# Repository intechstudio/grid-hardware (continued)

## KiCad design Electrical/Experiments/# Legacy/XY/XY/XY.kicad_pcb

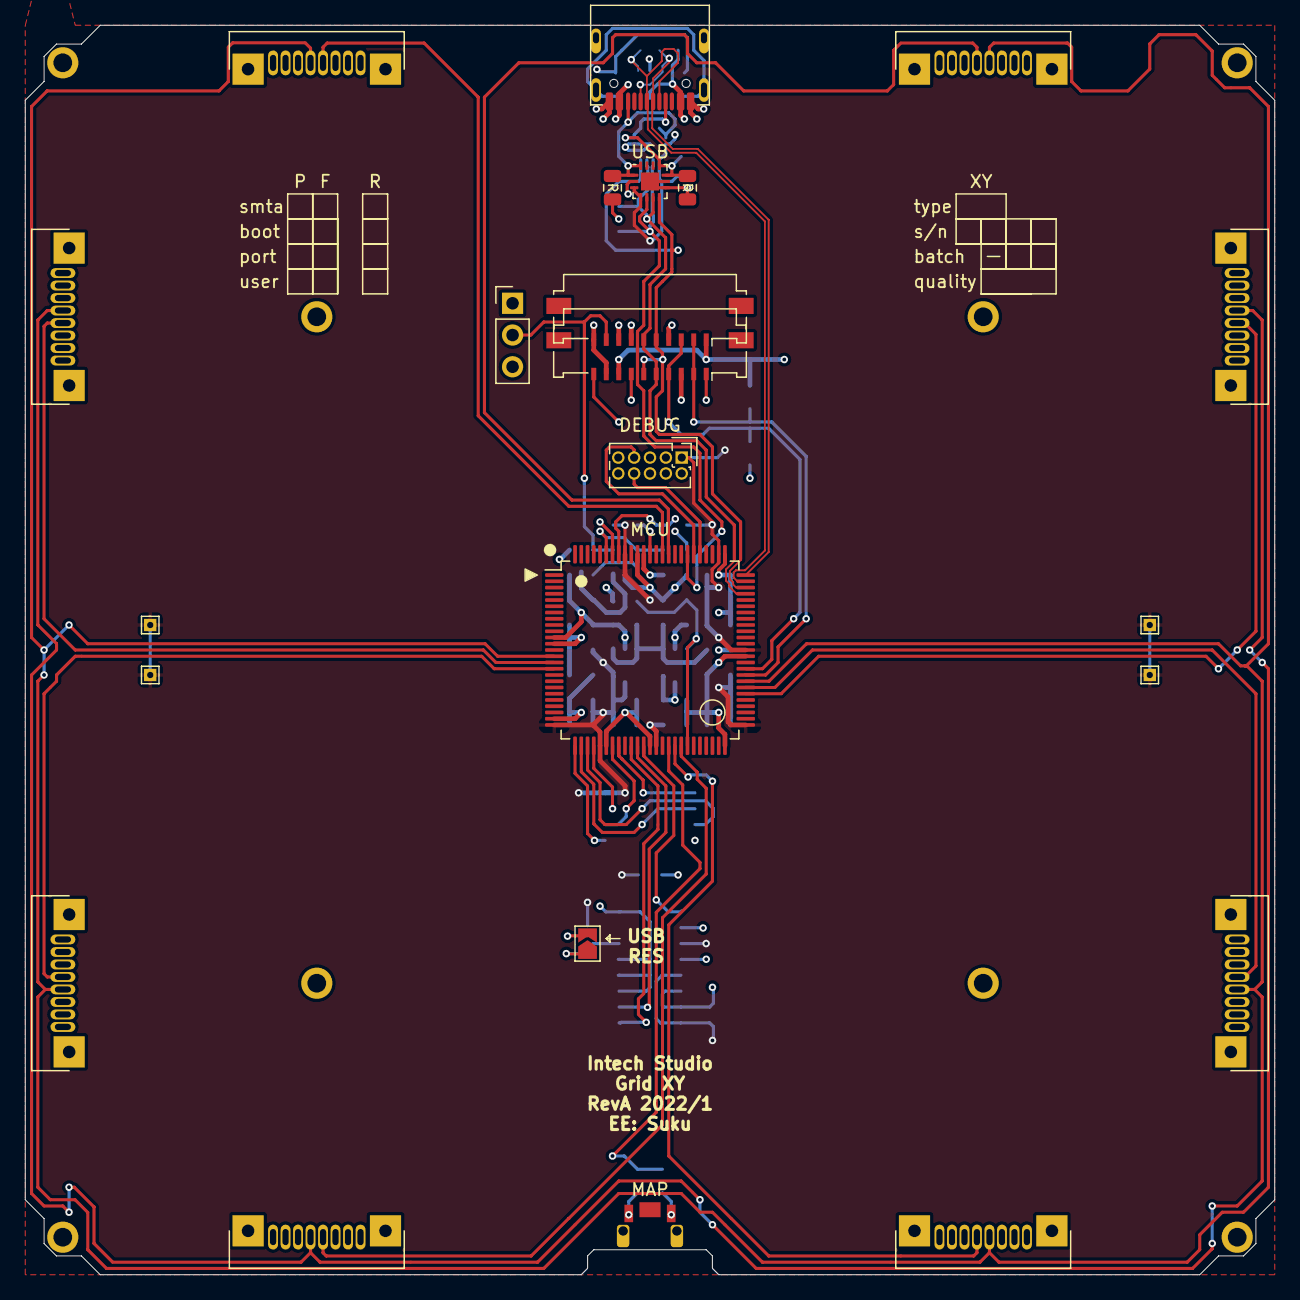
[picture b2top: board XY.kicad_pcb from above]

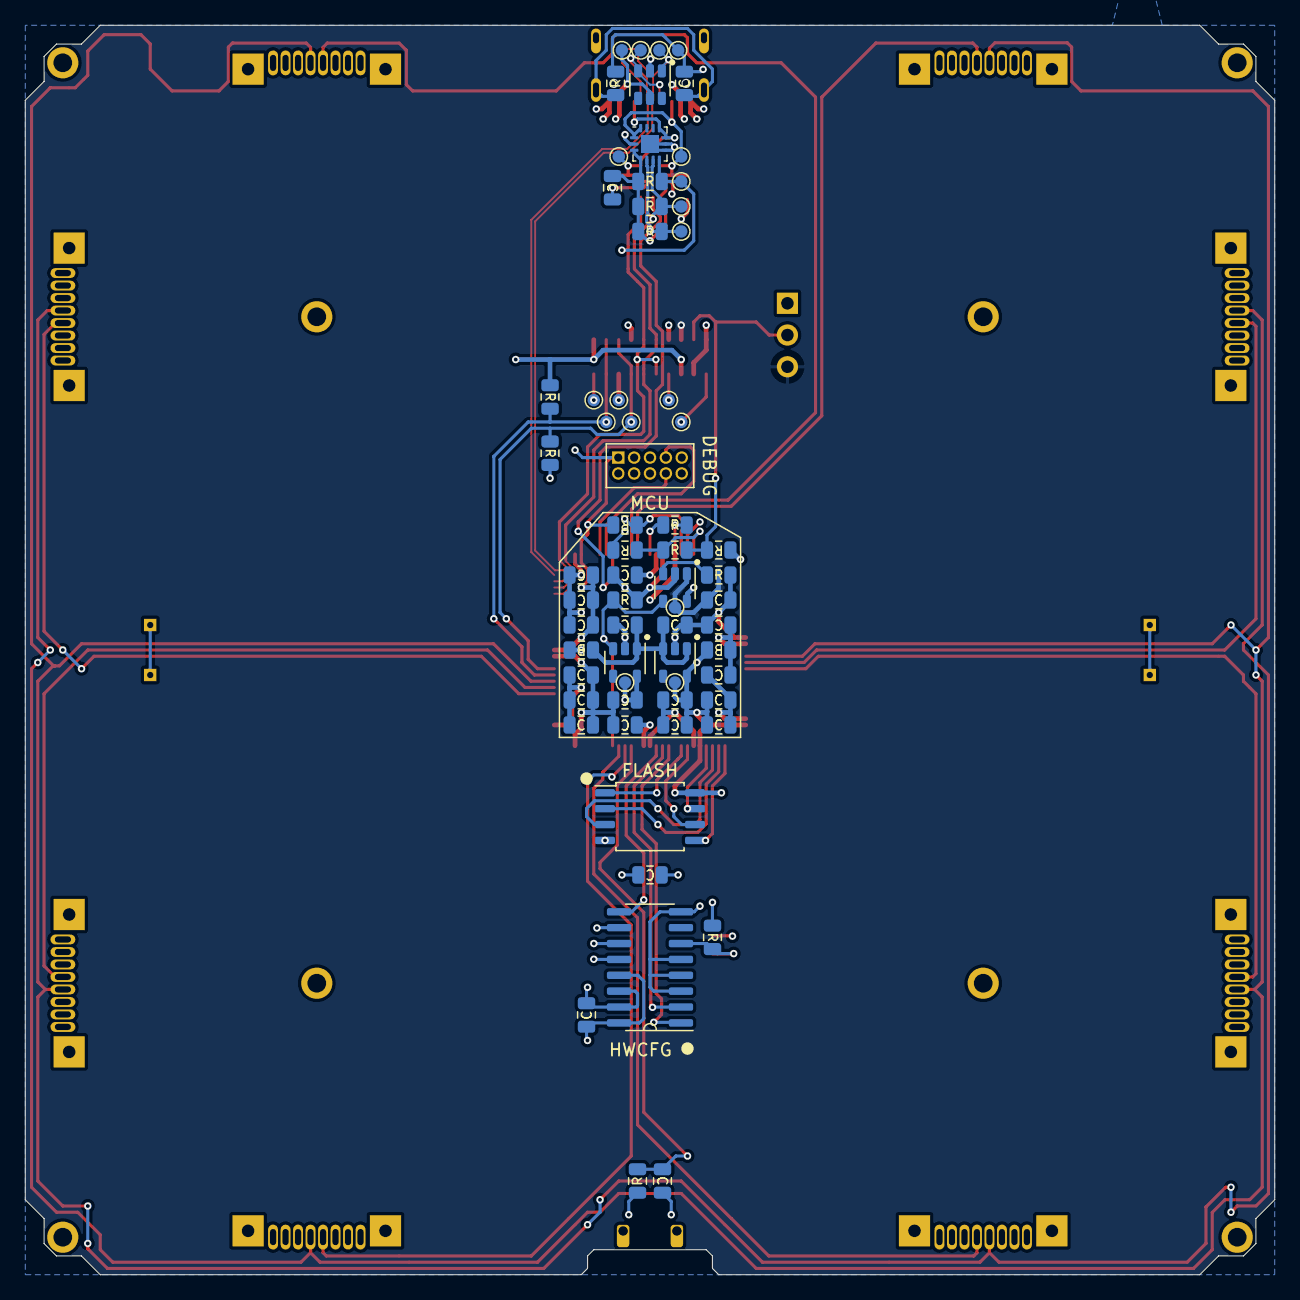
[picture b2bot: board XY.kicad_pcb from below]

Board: 4 copper layers, 100.0 x 100.0 mm, 89 parts (65 on the bottom side), 53 nets.

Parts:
C33, C39, C41, C42, C44, C45, C46, C47, C48, C49, C51, C54, C55, C94, C95: 100n; CAP_0805
C34, C36, C40, C50, C53: 1u; CAP_0805
C37: 4n7; CAP_0805
C38, C43: 10u; CAP_0805
J1: USB_C_TYPE-C-32-M-12; USB_C_Korean_Hroparts_TYPE-C-31-M-12
J2: (NF); PinHeader_2x05_P1.27mm_Vertical
J3: (NF); PinHeader_1x03_P2.54mm_Vertical
J4, J5, J6, J7, J8, J9, J10, J11: C20110 (NF); grid_ffc_8_vertical
J12: C262716; Molex_200528-0100_1x10-1MP_P1.00mm_Horizontal
J13: C262716 (NF); Molex_200528-0100_1x10-1MP_P1.00mm_Horizontal
JP2: (NF); SolderJumper-2_P1.3mm_Open_TrianglePad1.0x1.5mm
L1, L2: GZ2012D601TF; FERRIT_0805
M1: (NF); grid_outline
R1, R2, R36, R111, R112: 10k; RES_0805
R34, R37, R107, R108, R109, R110: 5k1; RES_0805
R35: 1M; RES_0805
R38, R39, R40, R41, R42: 1k; RES_0805
SW1: C255807; SW_HYP_MAPMODE
TP1, TP2, TP3, TP4: TestPoint; TestPoint_THTPad_1.0x1.0mm_Drill0.5mm
TP5: D-; TestPoint_Pad_D1.0mm
TP6: D+; TestPoint_Pad_D1.0mm
TP7: GND; TestPoint_Pad_D1.0mm
TP8: VB; TestPoint_Pad_D1.0mm
TP9: UC; TestPoint_Pad_D1.0mm
TP10: UI; TestPoint_Pad_D1.0mm
TP11: UI_5V; TestPoint_Pad_D1.0mm
TP12: MXT_DSS; TestPoint_Pad_D1.0mm
TP13: MXT_DDATA; TestPoint_Pad_D1.0mm
TP14: MXT_DCLK; TestPoint_Pad_D1.0mm
TP15: MXT_INT; TestPoint_Pad_D1.0mm
TP16: SDA; TestPoint_Pad_D1.0mm
TP17: SCL; TestPoint_Pad_D1.0mm
TP18: INT; TestPoint_Pad_D1.0mm
TP19: CC1; TestPoint_Pad_D1.0mm
TP20: CC2; TestPoint_Pad_D1.0mm
TP21: MXT_RST; TestPoint_Pad_D1.0mm
TP22: MXT_GND; TestPoint_Pad_D1.0mm
U3: 74HC165; SOIC-16_74HC165
U4: SESRV05-4; SOT-23-6
U5, U6: LN1134A332MR-G; SOT-23-5
U7: SAMD51N20A; TQFP-100_14x14mm_P0.5mm
U8: W25Q16JVSSIQ; SOIC-8W_FLASH
U15, U16: FUSB302BMPX (NF); WQFN-14-1EP_2.5x2.5mm_P0.5mm_EP1.45x1.45mm
U17: MT9700; SOT-23-5

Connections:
+3V3_UC: C33.1, C40.1, C41.1, C42.1, C43.1, C44.1, C45.1, C46.1, C47.1, C48.1, C51.1, C54.1, C55.1, C94.1, J2.1, L1.2, R38.2, R39.2, R108.1, R109.1, R110.1, R112.1, TP1.1, TP2.1, TP3.1, TP4.1, TP9.1, U3.11, U3.13, U3.16, U5.5, U7.25, U7.30, U7.39, U7.51, U7.63, U7.77, U7.92, U8.8, U15.3, U15.4, U16.3, U16.4
+3V3_UI: C36.1, J12.8, J13.1, R1.1, TP10.1, U6.5
+5V: J1.A4B9, J1.A9B4, J4.1, J4.2, J4.3, J5.6, J5.7, J5.8, J6.6, J6.7, J6.8, J7.1, J7.2, J7.3, J8.1, J8.2, J8.3, J9.6, J9.7, J9.8, J10.6, J10.7, J10.8, J11.1, J11.2, J11.3, L2.2, R34.1, TP8.1, U4.5, U15.2, U16.2, U17.5
+5V_UI: C50.1, J3.3, J13.8, TP11.1, U17.1
/HWCFG/HWCFG_CLOCK: U3.2, U7.36
/HWCFG/HWCFG_DATA: U3.9, U7.37
/HWCFG/HWCFG_SHIFT: U3.1, U7.35
/MCU/GRID_AUX_RX: J2.8, U7.80
/MCU/GRID_AUX_TX: J2.7, U7.81
/MCU/GRID_EAST_RX: J7.4, U7.56
/MCU/GRID_EAST_TX: J9.5, U7.57
/MCU/GRID_NORTH_RX: J4.4, U7.86
/MCU/GRID_NORTH_TX: J5.5, U7.85
/MCU/GRID_SOUTH_RX: J11.4, U7.42
/MCU/GRID_SOUTH_TX: J10.5, U7.43
/MCU/GRID_SYNC_1: J5.4, J6.4, J9.4, J10.4, U7.58
/MCU/GRID_SYNC_2: J4.5, J7.5, J8.5, J11.5, U7.14
/MCU/GRID_WEST_RX: J8.4, U7.16
/MCU/GRID_WEST_TX: J6.5, U7.15
/MCU/MAP_MODE: C95.1, R40.2, U7.41
/MCU/MUX_ADDRESS_A: J12.2, J13.2, R1.2, TP15.1, U7.59
/MCU/MUX_ADDRESS_B: J12.4, J13.3, R2.1, TP21.1, U7.60
/MCU/QSPI_IO_0: U7.26, U8.5
/MCU/QSPI_IO_1: U7.27, U8.2
/MCU/QSPI_IO_2: U7.28, U8.3
/MCU/QSPI_IO_3: U7.29, U8.7
/MCU/QSPI_SCK: U7.32, U8.6
/MCU/QSPI_~CE: U7.33, U8.1
/MCU/SYS_I2C_INT_0: R110.2, TP18.1, U7.82, U15.5, U16.5
/MCU/SYS_RESET: J2.10, R38.1, U7.88
/MCU/SYS_SWCLK: J2.4, R39.1, U7.93
/MCU/SYS_SWDIO: J2.2, U7.94
/MCU/SYS_SWO: J2.6, R41.2
/MCU/Sheet60FB6C45/USB_CC1: J1.A5, R37.1, TP19.1, U15.10, U15.11, U16.10, U16.11
/MCU/Sheet60FB6C45/USB_CC2: J1.B5, R107.1, TP20.1, U15.1, U15.14, U16.1, U16.14
/MCU/UI_PWR_EN: R36.1, U6.3, U7.44, U17.4
/MCU/USB_DN: J1.A7, J1.B7, TP5.1, U4.1, U7.74
/MCU/USB_DP: J1.A6, J1.B6, TP6.1, U4.3, U7.75
/UI_LED/DBG_CLK: J12.7, TP14.1
/UI_LED/DBG_DATA: J12.10, TP13.1
/UI_LED/DBG_SS: J12.1, TP12.1
/UI_LED/LED_DATA_IN: J3.2, J13.9, R34.2, R42.2
/UI_LED/MXT_SCL: J12.5, J13.6, R109.2, TP17.1, U7.72, U15.6, U16.6
/UI_LED/MXT_SDA: J12.6, J13.5, R108.2, TP16.1, U7.73, U15.7, U16.7
GND: C33.2, C34.2, C36.2, C37.2, C38.2, C39.2, C40.2, C41.2, C42.2, C43.2, C44.2, C45.2, C46.2, C47.2, C48.2, C49.2, C50.2, C51.2, C53.2, C54.2, C55.2, C94.2, C95.2, J1.A1B12, J1.A12B1, J2.3, J2.5, J2.9, J3.1, J4.6, J4.7, J4.8, J5.1, J5.2, J5.3, J6.1, J6.2, J6.3, J7.6, J7.7, J7.8, J8.6, J8.7, J8.8, J9.1, J9.2, J9.3, J10.1, J10.2, J10.3, J11.6, J11.7, J11.8, J12.3, J12.9, J13.4, J13.7, J13.10, JP2.2, R2.2, R35.2, R36.2, R37.2, R107.2, R111.2, SW1.2, TP7.1, TP22.1, U3.3, U3.4, U3.5, U3.8, U3.10, U3.12, U3.14, U3.15, U4.2, U5.2, U6.2, U7.11, U7.24, U7.31, U7.38, U7.50, U7.62, U7.76, U7.90, U8.4, U15.8, U15.9, U15.15, U16.8, U16.9, U16.15, U17.2
unnamed: C34.1, C53.1, L2.1, U5.1, U5.3, U6.1
unnamed: C37.1, J1.S1, J1.S2, R35.1
unnamed: C38.1, C39.1, L1.1, U7.12
unnamed: C49.1, U7.89
unnamed: JP2.1, R112.2, U3.6
unnamed: R40.1, SW1.1
unnamed: R41.1, R42.1, U7.95
unnamed: R111.1, U17.3

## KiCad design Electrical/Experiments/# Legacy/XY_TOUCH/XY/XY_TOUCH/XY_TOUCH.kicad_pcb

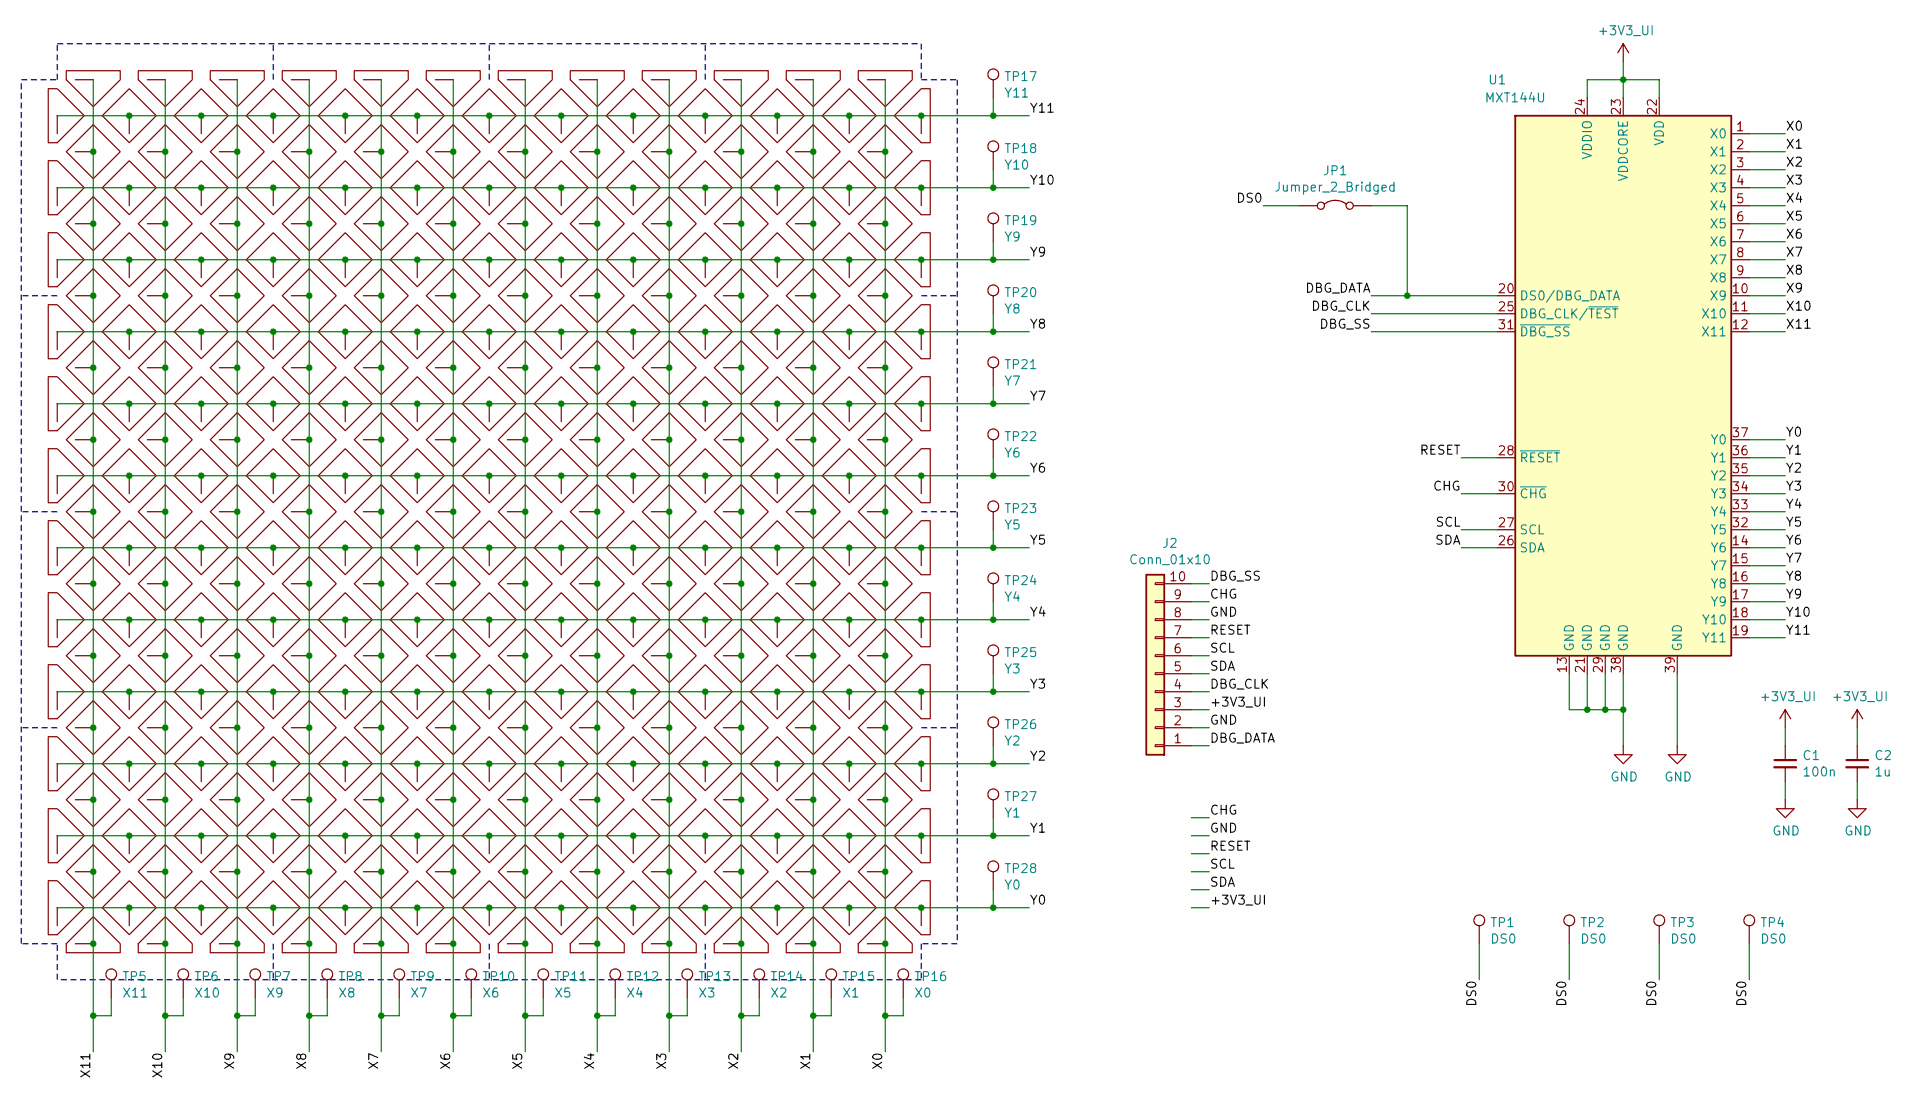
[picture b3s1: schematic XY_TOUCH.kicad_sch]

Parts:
C1: 100n; CAP_0805
C2: 1u; CAP_0805
CS1, CS4, CS7, CS10, CS25, CS63, CS100, CS138, CS175, CS213, CS250, CS288, CS303, CS306, CS309, CS312: capsense_diamond_edge; capsense_diamond_edge_bite_left
CS2, CS5, CS8, CS11, CS38, CS50, CS113, CS125, CS188, CS200, CS263, CS275, CS302, CS305, CS308, CS311: capsense_diamond_edge
CS3, CS6, CS9, CS12, CS13, CS75, CS88, CS150, CS163, CS225, CS238, CS300, CS301, CS304, CS307, CS310: capsense_diamond_edge; capsense_diamond_edge_bite_right
CS14, CS15, CS17, CS18, CS20, CS21, CS23, CS24, CS26, CS27, CS28, CS29, CS30, CS31, CS32, CS33, CS34, CS35, CS36, CS37, CS39, CS40, CS41, CS42, CS43, CS44, CS45, CS46, CS47, CS48, CS49, CS51, CS52, CS53, CS54, CS55, CS56, CS57, CS58, CS59, CS60, CS61, CS62, CS64, CS65, CS67, CS68, CS70, CS71, CS73, CS74, CS77, CS80, CS83, CS86, CS89, CS90, CS92, CS93, CS95, CS96, CS98, CS99, CS101, CS102, CS103, CS104, CS105, CS106, CS107, CS108, CS109, CS110, CS111, CS112, CS114, CS115, CS116, CS117, CS118, CS119, CS120, CS121, CS122, CS123, CS124, CS126, CS127, CS128, CS129, CS130, CS131, CS132, CS133, CS134, CS135, CS136, CS137, CS139, CS140, CS142, CS143, CS145, CS146, CS148, CS149, CS152, CS155, CS158, CS161, CS164, CS165, CS167, CS168, CS170, CS171, CS173, CS174, CS176, CS177, CS178, CS179, CS180, CS181, CS182, CS183, CS184, CS185, CS186, CS187, CS189, CS190, CS191, CS192, CS193, CS194, CS195, CS196, CS197, CS198, CS199, CS201, CS202, CS203, CS204, CS205, CS206, CS207, CS208, CS209, CS210, CS211, CS212, CS214, CS215, CS217, CS218, CS220, CS221, CS223, CS224, CS227, CS230, CS233, CS236, CS239, CS240, CS242, CS243, CS245, CS246, CS248, CS249, CS251, CS252, CS253, CS254, CS255, CS256, CS257, CS258, CS259, CS260, CS261, CS262, CS264, CS265, CS266, CS267, CS268, CS269, CS270, CS271, CS272, CS273, CS274, CS276, CS277, CS278, CS279, CS280, CS281, CS282, CS283, CS284, CS285, CS286, CS287, CS289, CS290, CS292, CS293, CS295, CS296, CS298, CS299: capsense_diamond
CS16, CS19, CS22, CS66, CS69, CS72, CS76, CS78, CS79, CS81, CS82, CS84, CS85, CS87, CS91, CS94, CS97, CS141, CS144, CS147, CS151, CS153, CS154, CS156, CS157, CS159, CS160, CS162, CS166, CS169, CS172, CS216, CS219, CS222, CS226, CS228, CS229, CS231, CS232, CS234, CS235, CS237, CS241, CS244, CS247, CS291, CS294, CS297: capsense_diamond; capsense_diamond_bite
J2: Conn_01x10; Molex_200528-0100_1x10-1MP_P1.00mm_Horizontal
JP1: Jumper_2_Bridged; SolderJumper-2_P1.3mm_Bridged_RoundedPad1.0x1.5mm
TP1, TP2, TP3, TP4: DS0; TestPoint_THTPad_1.0x1.0mm_Drill0.5mm
TP5: X11; TestPoint_Pad_D1.0mm
TP6: X10; TestPoint_Pad_D1.0mm
TP7: X9; TestPoint_Pad_D1.0mm
TP8: X8; TestPoint_Pad_D1.0mm
TP9: X7; TestPoint_Pad_D1.0mm
TP10: X6; TestPoint_Pad_D1.0mm
TP11: X5; TestPoint_Pad_D1.0mm
TP12: X4; TestPoint_Pad_D1.0mm
TP13: X3; TestPoint_Pad_D1.0mm
TP14: X2; TestPoint_Pad_D1.0mm
TP15: X1; TestPoint_Pad_D1.0mm
TP16: X0; TestPoint_Pad_D1.0mm
TP17: Y11; TestPoint_Pad_D1.0mm
TP18: Y10; TestPoint_Pad_D1.0mm
TP19: Y9; TestPoint_Pad_D1.0mm
TP20: Y8; TestPoint_Pad_D1.0mm
TP21: Y7; TestPoint_Pad_D1.0mm
TP22: Y6; TestPoint_Pad_D1.0mm
TP23: Y5; TestPoint_Pad_D1.0mm
TP24: Y4; TestPoint_Pad_D1.0mm
TP25: Y3; TestPoint_Pad_D1.0mm
TP26: Y2; TestPoint_Pad_D1.0mm
TP27: Y1; TestPoint_Pad_D1.0mm
TP28: Y0; TestPoint_Pad_D1.0mm
U1: MXT144U; QFN-38_EP_4x4_Pitch0.35mm

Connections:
+3V3_UI: C1.1, C2.1, J2.3, U1.22 (VDD), U1.23 (VDDCORE), U1.24 (VDDIO)
/CHG: J2.9, U1.30 (~CHG)
/DBG_CLK: J2.4, U1.25 (DBG_CLK/~TEST)
/DBG_DATA: J2.1, JP1.2 (B), U1.20 (DS0/DBG_DATA)
/DBG_SS: J2.10, U1.31 (~DBG_SS)
/DS0: JP1.1 (A), TP1.1, TP2.1, TP3.1, TP4.1
/RESET: J2.7, U1.28 (~RESET)
/SCL: J2.6, U1.27 (SCL)
/SDA: J2.5, U1.26 (SDA)
/X0: CS288.1, CS289.1, CS290.1, CS291.1, CS292.1, CS293.1, CS294.1, CS295.1, CS296.1, CS297.1, CS298.1, CS299.1, CS300.1, TP16.1, U1.1 (X0)
/X1: CS263.1, CS264.1, CS265.1, CS266.1, CS267.1, CS268.1, CS269.1, CS270.1, CS271.1, CS272.1, CS273.1, CS274.1, CS275.1, TP15.1, U1.2 (X1)
/X2: CS238.1, CS239.1, CS240.1, CS241.1, CS242.1, CS243.1, CS244.1, CS245.1, CS246.1, CS247.1, CS248.1, CS249.1, CS250.1, TP14.1, U1.3 (X2)
/X3: CS213.1, CS214.1, CS215.1, CS216.1, CS217.1, CS218.1, CS219.1, CS220.1, CS221.1, CS222.1, CS223.1, CS224.1, CS225.1, TP13.1, U1.4 (X3)
/X4: CS188.1, CS189.1, CS190.1, CS191.1, CS192.1, CS193.1, CS194.1, CS195.1, CS196.1, CS197.1, CS198.1, CS199.1, CS200.1, TP12.1, U1.5 (X4)
/X5: CS163.1, CS164.1, CS165.1, CS166.1, CS167.1, CS168.1, CS169.1, CS170.1, CS171.1, CS172.1, CS173.1, CS174.1, CS175.1, TP11.1, U1.6 (X5)
/X6: CS138.1, CS139.1, CS140.1, CS141.1, CS142.1, CS143.1, CS144.1, CS145.1, CS146.1, CS147.1, CS148.1, CS149.1, CS150.1, TP10.1, U1.7 (X6)
/X7: CS113.1, CS114.1, CS115.1, CS116.1, CS117.1, CS118.1, CS119.1, CS120.1, CS121.1, CS122.1, CS123.1, CS124.1, CS125.1, TP9.1, U1.8 (X7)
/X8: CS88.1, CS89.1, CS90.1, CS91.1, CS92.1, CS93.1, CS94.1, CS95.1, CS96.1, CS97.1, CS98.1, CS99.1, CS100.1, TP8.1, U1.9 (X8)
/X9: CS63.1, CS64.1, CS65.1, CS66.1, CS67.1, CS68.1, CS69.1, CS70.1, CS71.1, CS72.1, CS73.1, CS74.1, CS75.1, TP7.1, U1.10 (X9)
/X10: CS38.1, CS39.1, CS40.1, CS41.1, CS42.1, CS43.1, CS44.1, CS45.1, CS46.1, CS47.1, CS48.1, CS49.1, CS50.1, TP6.1, U1.11 (X10)
/X11: CS13.1, CS14.1, CS15.1, CS16.1, CS17.1, CS18.1, CS19.1, CS20.1, CS21.1, CS22.1, CS23.1, CS24.1, CS25.1, TP5.1, U1.12 (X11)
/Y0: CS12.1, CS37.1, CS62.1, CS87.1, CS112.1, CS137.1, CS162.1, CS187.1, CS212.1, CS237.1, CS262.1, CS287.1, CS312.1, TP28.1, U1.37 (Y0)
/Y1: CS11.1, CS36.1, CS61.1, CS86.1, CS111.1, CS136.1, CS161.1, CS186.1, CS211.1, CS236.1, CS261.1, CS286.1, CS311.1, TP27.1, U1.36 (Y1)
/Y2: CS10.1, CS35.1, CS60.1, CS85.1, CS110.1, CS135.1, CS160.1, CS185.1, CS210.1, CS235.1, CS260.1, CS285.1, CS310.1, TP26.1, U1.35 (Y2)
/Y3: CS9.1, CS34.1, CS59.1, CS84.1, CS109.1, CS134.1, CS159.1, CS184.1, CS209.1, CS234.1, CS259.1, CS284.1, CS309.1, TP25.1, U1.34 (Y3)
/Y4: CS8.1, CS33.1, CS58.1, CS83.1, CS108.1, CS133.1, CS158.1, CS183.1, CS208.1, CS233.1, CS258.1, CS283.1, CS308.1, TP24.1, U1.33 (Y4)
/Y5: CS7.1, CS32.1, CS57.1, CS82.1, CS107.1, CS132.1, CS157.1, CS182.1, CS207.1, CS232.1, CS257.1, CS282.1, CS307.1, TP23.1, U1.32 (Y5)
/Y6: CS6.1, CS31.1, CS56.1, CS81.1, CS106.1, CS131.1, CS156.1, CS181.1, CS206.1, CS231.1, CS256.1, CS281.1, CS306.1, TP22.1, U1.14 (Y6)
/Y7: CS5.1, CS30.1, CS55.1, CS80.1, CS105.1, CS130.1, CS155.1, CS180.1, CS205.1, CS230.1, CS255.1, CS280.1, CS305.1, TP21.1, U1.15 (Y7)
/Y8: CS4.1, CS29.1, CS54.1, CS79.1, CS104.1, CS129.1, CS154.1, CS179.1, CS204.1, CS229.1, CS254.1, CS279.1, CS304.1, TP20.1, U1.16 (Y8)
/Y9: CS3.1, CS28.1, CS53.1, CS78.1, CS103.1, CS128.1, CS153.1, CS178.1, CS203.1, CS228.1, CS253.1, CS278.1, CS303.1, TP19.1, U1.17 (Y9)
/Y10: CS2.1, CS27.1, CS52.1, CS77.1, CS102.1, CS127.1, CS152.1, CS177.1, CS202.1, CS227.1, CS252.1, CS277.1, CS302.1, TP18.1, U1.18 (Y10)
/Y11: CS1.1, CS26.1, CS51.1, CS76.1, CS101.1, CS126.1, CS151.1, CS176.1, CS201.1, CS226.1, CS251.1, CS276.1, CS301.1, TP17.1, U1.19 (Y11)
GND: C1.2, C2.2, J2.2, J2.8, U1.13 (GND), U1.21 (GND), U1.29 (GND), U1.38 (GND), U1.39 (GND)

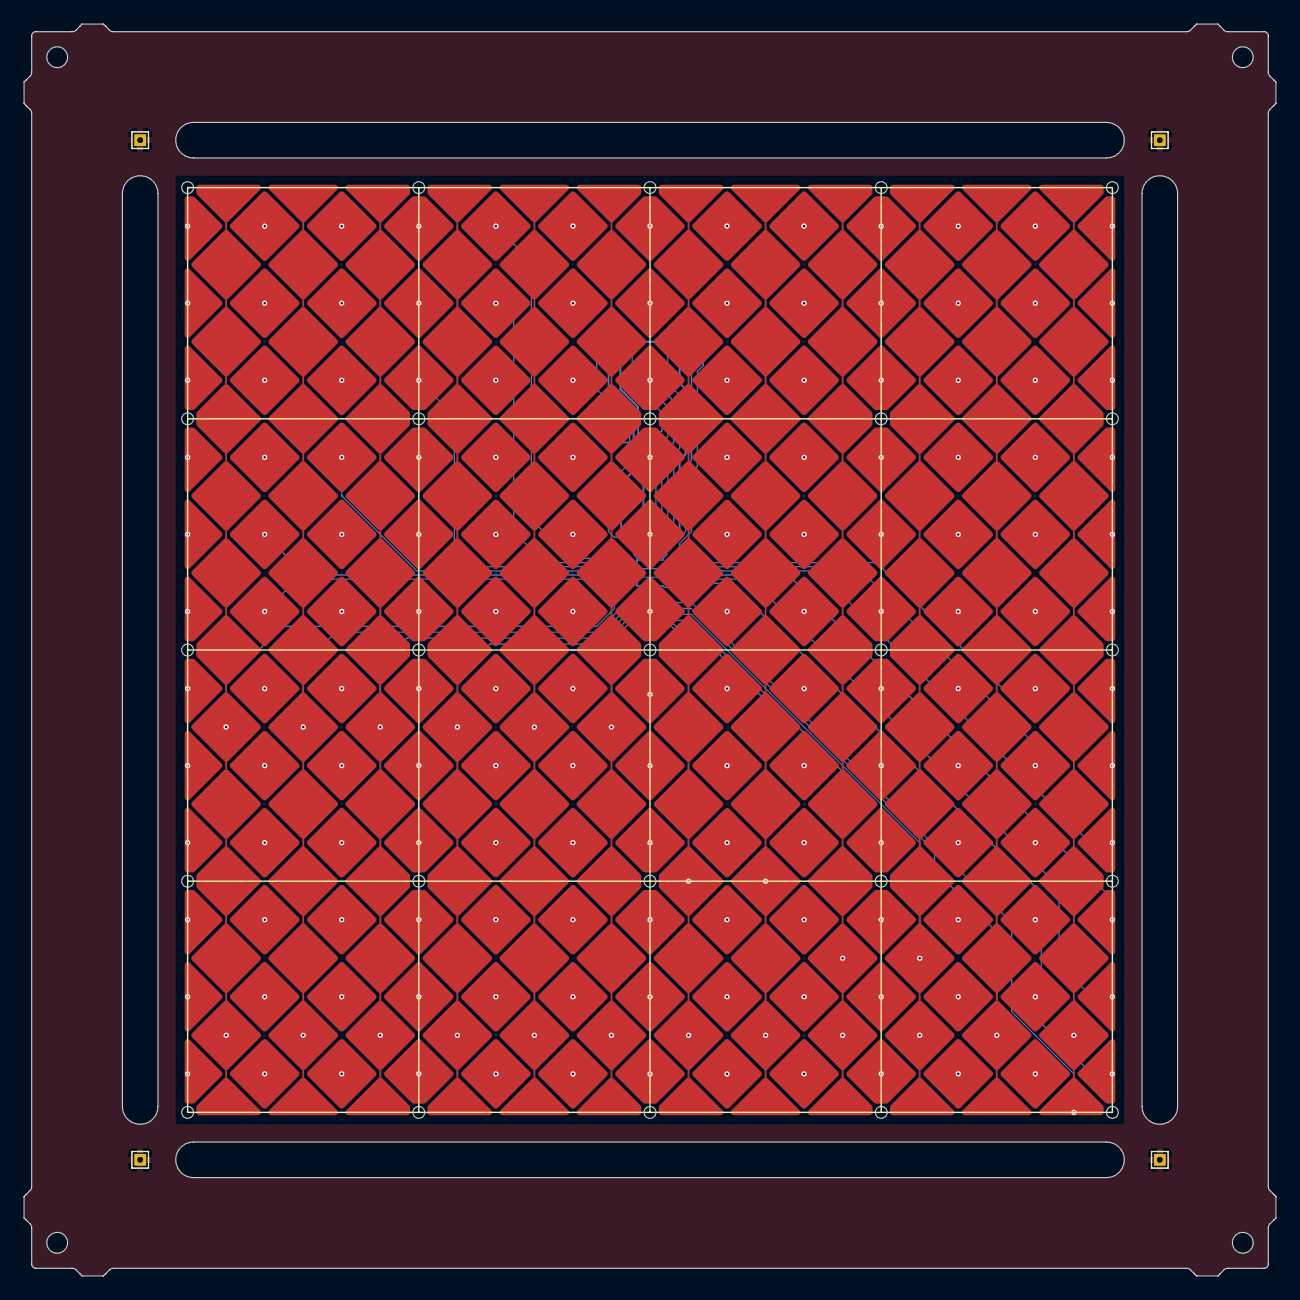
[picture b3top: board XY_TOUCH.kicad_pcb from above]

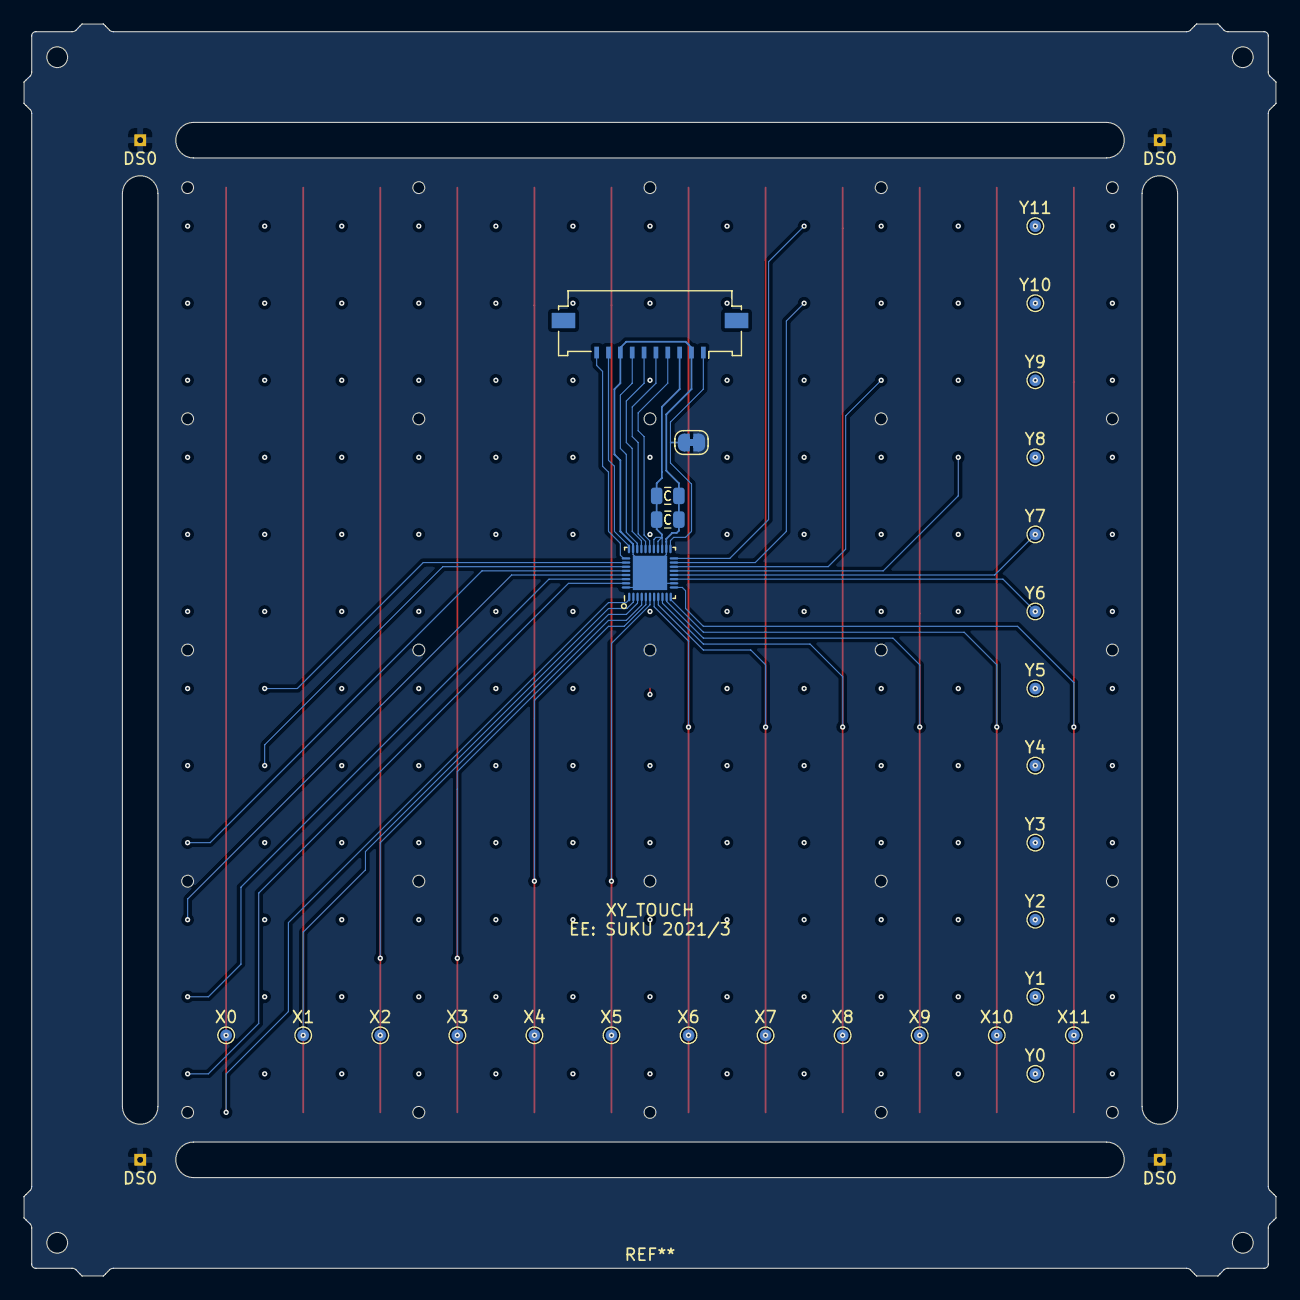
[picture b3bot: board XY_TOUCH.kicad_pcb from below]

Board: 4 copper layers, 105.6 x 105.6 mm, 345 parts (29 on the bottom side), 34 nets.

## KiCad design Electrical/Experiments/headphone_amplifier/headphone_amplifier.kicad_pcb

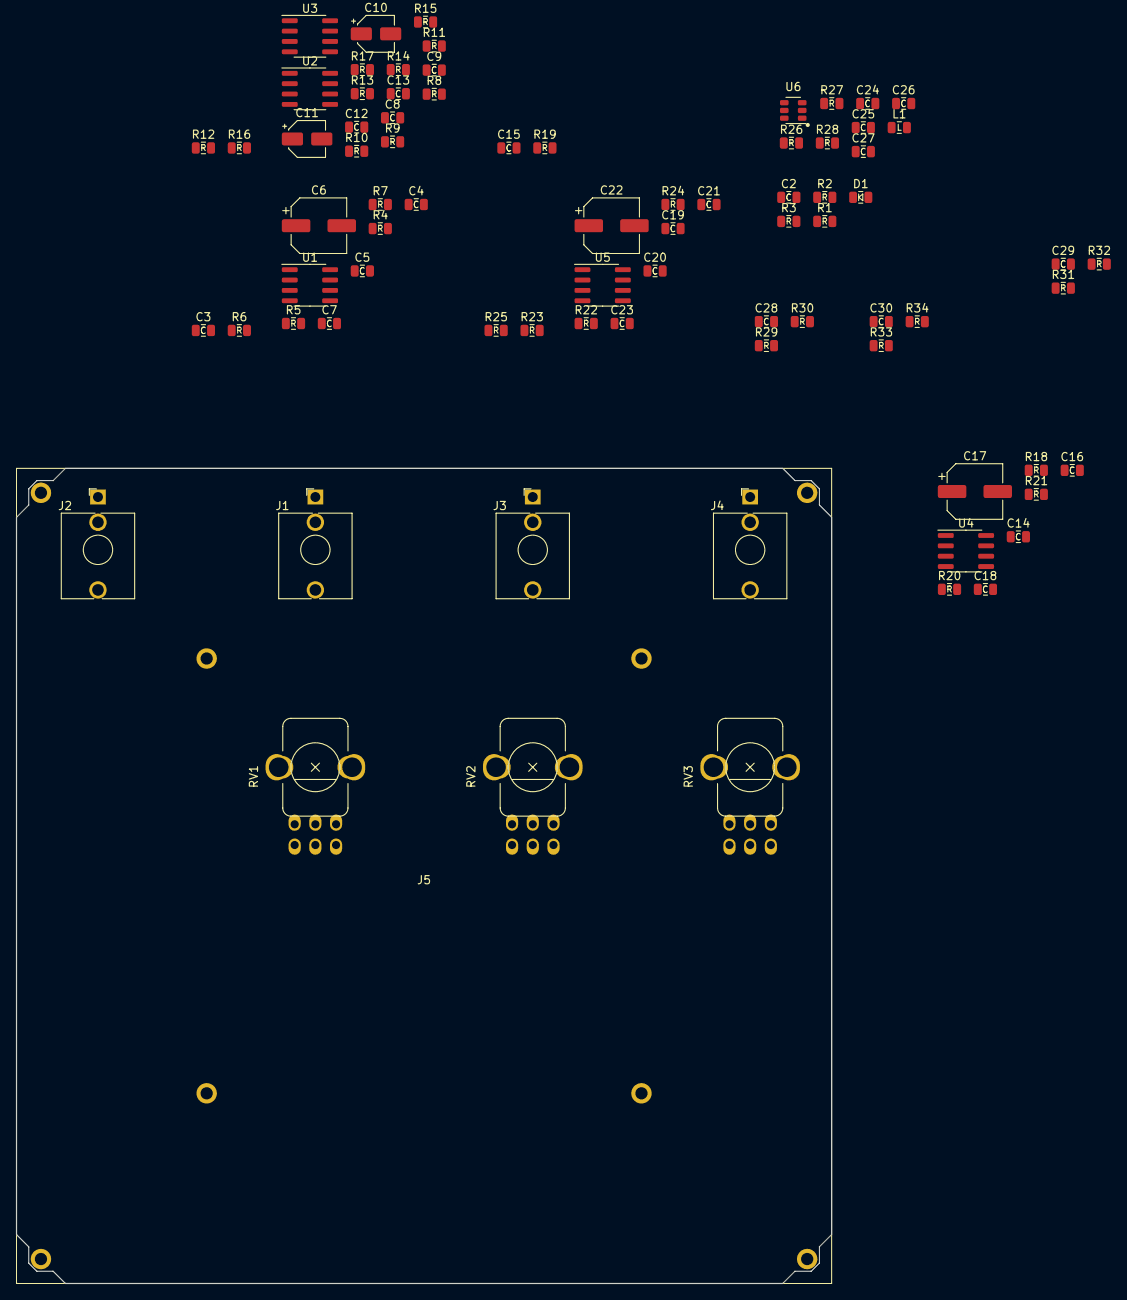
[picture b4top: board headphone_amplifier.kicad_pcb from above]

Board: 2 copper layers, 100.0 x 100.0 mm, 79 parts (0 on the bottom side), 48 nets, no tracks yet.

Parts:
C2, C8, C9, C28, C29, C30: 10u; CAP_0805
C3, C4, C14, C15, C19, C20: 20p; CAP_0805
C5, C12, C16, C21, C25, C26: 100n; CAP_0805
C6, C17, C22: 220u; CP_Elec_6.3x5.4
C7, C13, C18, C23: 1u; CAP_0805
C10, C11: 1u; CP_Elec_4x5.4
C24, C27: 20u; CAP_0805
D1: LED; LED_0805
J1, J2, J3, J4: AudioJack3; jack_3.5_vertical_stereo
J5: Conn_01x08; grid_outline
L1: 3.3uH; IND_0805
R1, R2, R16, R17: 0R; RES_0805
R3: 22k; RES_0805
R4, R5, R18, R19, R22, R23, R26: 10k; RES_0805
R6, R7, R20, R21, R24, R25: 47R; RES_0805
R8, R9, R10, R11, R12, R13, R14, R15, R27, R29, R30, R31, R32, R33, R34: 100k; RES_0805
R28: 5.1k; RES_0805
RV1, RV2, RV3: 20k; pot_dual_gang_vertical
U1, U2, U3, U4, U5: NJM4556A; SOIC-8_3.9x4.9mm_P1.27mm
U6: FP6291; SOT-23-6

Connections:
+12V: C2.1, C5.1, C7.1, C12.1, C13.1, C16.1, C18.1, C21.1, C23.1, R2.1, R3.1, R8.2, R10.2, R29.2, R31.2, R33.2, U1.8, U2.8, U3.8, U4.8
/Sheet5FF09E24/IN_LEFT: R4.2, R16.1, R18.2, R22.2, U2.1
/Sheet5FF09E24/IN_RIGHT: R5.2, R17.1, R19.2, R23.2, U3.1
/Sheet60078C3F/Vin: C24.1, C25.1, L1.2, R1.1, U6.4, U6.5
/Sheet60078C3F/Vout: C26.1, C27.1, R2.2, R27.1
GND: C2.2, C5.2, C6.2, C7.2, C8.2, C9.2, C12.2, C13.2, C16.2, C17.2, C18.2, C21.2, C22.2, C23.2, C24.2, C25.2, C26.2, C27.2, C28.2, C29.2, C30.2, D1.1, J2.S, R9.1, R11.1, R26.2, R28.1, R30.1, R32.1, R34.1, U1.4, U2.4, U3.4, U4.4, U6.2
unnamed: C3.1, R6.2, RV1.3, U1.1
unnamed: C3.2, RV1.2, U1.2
unnamed: C4.1, R7.2, RV1.6, U1.7
unnamed: C4.2, RV1.5, U1.6
unnamed: C6.1, J1.S
unnamed: C8.1, R8.1, R9.2, R12.2, R14.1
unnamed: C9.1, R10.1, R11.2, R13.2, R15.1
unnamed: C10.1, R12.1, U2.3
unnamed: C10.2, J2.T
unnamed: C11.1, R13.1, U3.3
unnamed: C11.2, J2.R
unnamed: C14.1, R20.2, RV2.3, U4.1
unnamed: C14.2, RV2.2, U4.2
unnamed: C15.1, R21.2, RV2.6, U2.7
unnamed: C15.2, RV2.5, U2.6
unnamed: C17.1, J3.S
unnamed: C19.1, R24.2, RV3.3, U5.1
unnamed: C19.2, RV3.2, U5.2
unnamed: C20.1, R25.2, RV3.6, U3.7
unnamed: C20.2, RV3.5, U3.6
unnamed: C22.1, J4.S
unnamed: C28.1, R29.1, R30.2, U1.3, U1.5
unnamed: C29.1, R31.1, R32.2, U2.5, U4.3
unnamed: C30.1, R33.1, R34.2, U3.5, U5.3
unnamed: D1.2, R3.2
unnamed: L1.1, U6.1
unnamed: J1.R, R7.1
unnamed: J1.T, R6.1
unnamed: J3.R, R21.1
unnamed: J3.T, R20.1
unnamed: J4.R, R25.1
unnamed: J4.T, R24.1
unnamed: R4.1, RV1.1
unnamed: R5.1, RV1.4
unnamed: R14.2, R16.2, U2.2
unnamed: R15.2, R17.2, U3.2
unnamed: R18.1, RV2.1
unnamed: R19.1, RV2.4
unnamed: R22.1, RV3.1
unnamed: R23.1, RV3.4
unnamed: R26.1, U6.6
unnamed: R27.2, R28.2, U6.3

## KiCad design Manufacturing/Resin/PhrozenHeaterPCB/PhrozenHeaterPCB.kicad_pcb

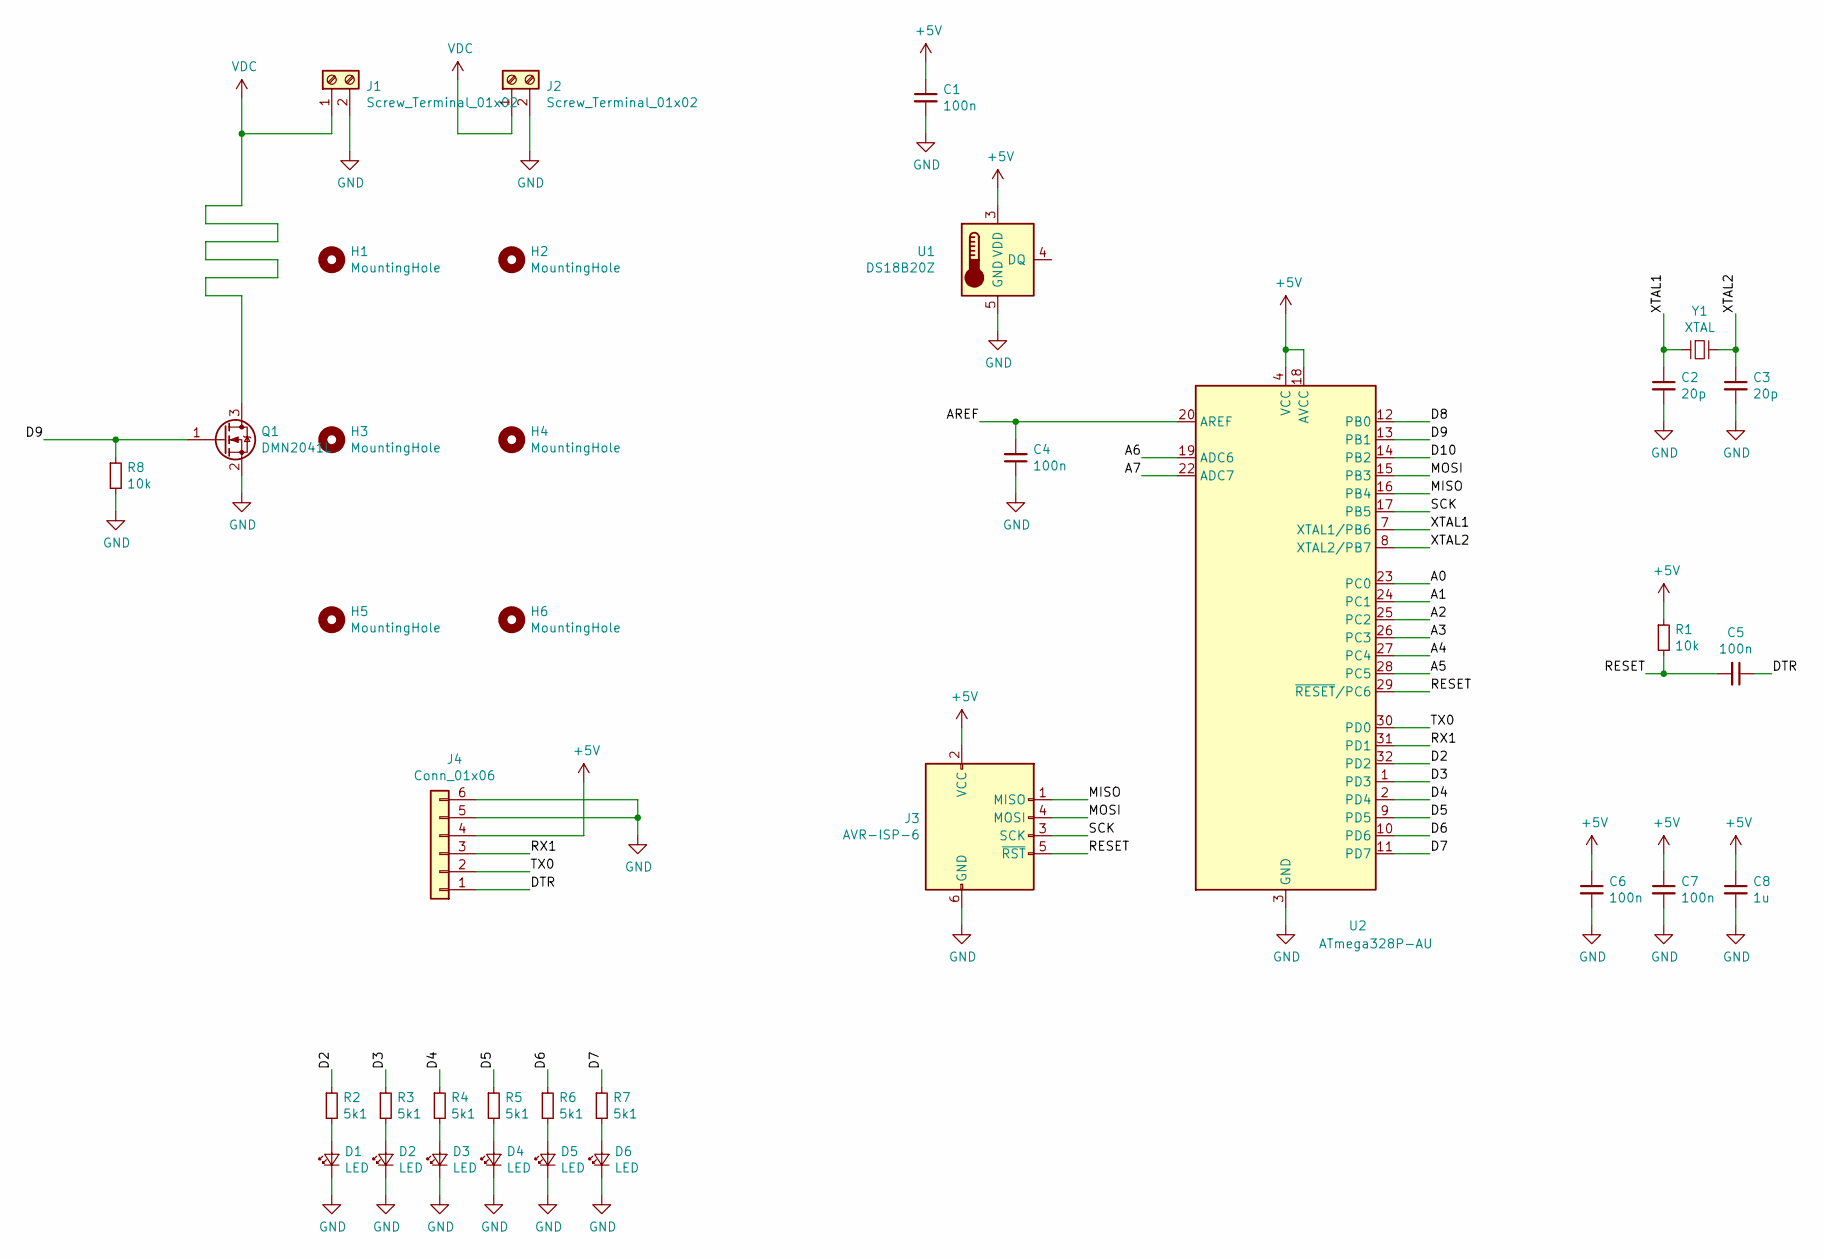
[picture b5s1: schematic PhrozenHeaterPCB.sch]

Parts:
C1, C4, C5, C6, C7: 100n; CAP_0805
C2, C3: 20p; CAP_0805
C8: 1u; CAP_0805
D1, D2, D3, D4, D5, D6: LED; LED_0805
H1, H2, H3, H4, H5, H6: MountingHole; MountingHole_3.2mm_M3
J1, J2: Screw_Terminal_01x02; TerminalBlock_bornier-2_P5.08mm
J3: AVR-ISP-6; IDC-Header_2x03_P2.54mm_Vertical
J4: Conn_01x06; PinSocket_1x06_P2.54mm_Vertical
Q1: DMN2041L; SOT-23
R1, R8: 10k; RES_0805
R2, R3, R4, R5, R6, R7: 5k1; RES_0805
U1: DS18B20Z; SOIC-8_3.9x4.9mm_P1.27mm
U2: ATmega328P-AU; TQFP-32_7x7mm_P0.8mm
Y1: XTAL; Crystal_SMD_HC49-SD

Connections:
+5V: C1.1, C6.1, C7.1, C8.1, J3.2 (VCC), J4.4, R1.1, U1.3 (VDD), U2.4 (VCC), U2.6 (VCC), U2.18 (AVCC)
/A0: U2.23 (PC0)
/A1: U2.24 (PC1)
/A2: U2.25 (PC2)
/A3: U2.26 (PC3)
/A4: U2.27 (PC4)
/A5: U2.28 (PC5)
/A6: U2.19 (ADC6)
/A7: U2.22 (ADC7)
/AREF: C4.2, U2.20 (AREF)
/D2: R2.1, U2.32 (PD2)
/D3: R3.1, U2.1 (PD3)
/D4: R4.1, U2.2 (PD4)
/D5: R5.1, U2.9 (PD5)
/D6: R6.1, U2.10 (PD6)
/D7: R7.1, U2.11 (PD7)
/D8: U2.12 (PB0)
/D9: Q1.1 (G), R8.1, U2.13 (PB1)
/D10: U2.14 (PB2)
/DTR: C5.1, J4.1
/MISO: J3.1 (MISO), U2.16 (PB4)
/MOSI: J3.4 (MOSI), U2.15 (PB3)
/RESET: C5.2, J3.5 (~RST), R1.2, U2.29 (~RESET~/PC6)
/RX1: J4.3, U2.31 (PD1)
/SCK: J3.3 (SCK), U2.17 (PB5)
/TX0: J4.2, U2.30 (PD0)
/XTAL1: C2.1, U2.7 (XTAL1/PB6), Y1.1
/XTAL2: C3.1, U2.8 (XTAL2/PB7), Y1.2
GND: C1.2, C2.2, C3.2, C4.1, C6.2, C7.2, C8.2, D1.1 (K), D2.1 (K), D3.1 (K), D4.1 (K), D5.1 (K), D6.1 (K), J1.2, J2.2, J3.6 (GND), J4.5, J4.6, Q1.2 (S), R8.2, U1.5 (GND), U2.3 (GND), U2.5 (GND), U2.21 (GND)
unnamed: D1.2 (A), R2.2
unnamed: D2.2 (A), R3.2
unnamed: D3.2 (A), R4.2
unnamed: D4.2 (A), R5.2
unnamed: D5.2 (A), R6.2
unnamed: D6.2 (A), R7.2
VDC: J1.1, J2.1, Q1.3 (D)
